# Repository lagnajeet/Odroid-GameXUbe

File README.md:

# Ordoid GameXUbe

A gamecude looking console using Odroid XU4 single board computer. 

Below is a demo video of working of the case. It has the retro arena retropie OS installed in the Board. It can be used with other retro OSes like recalbox or batocera.

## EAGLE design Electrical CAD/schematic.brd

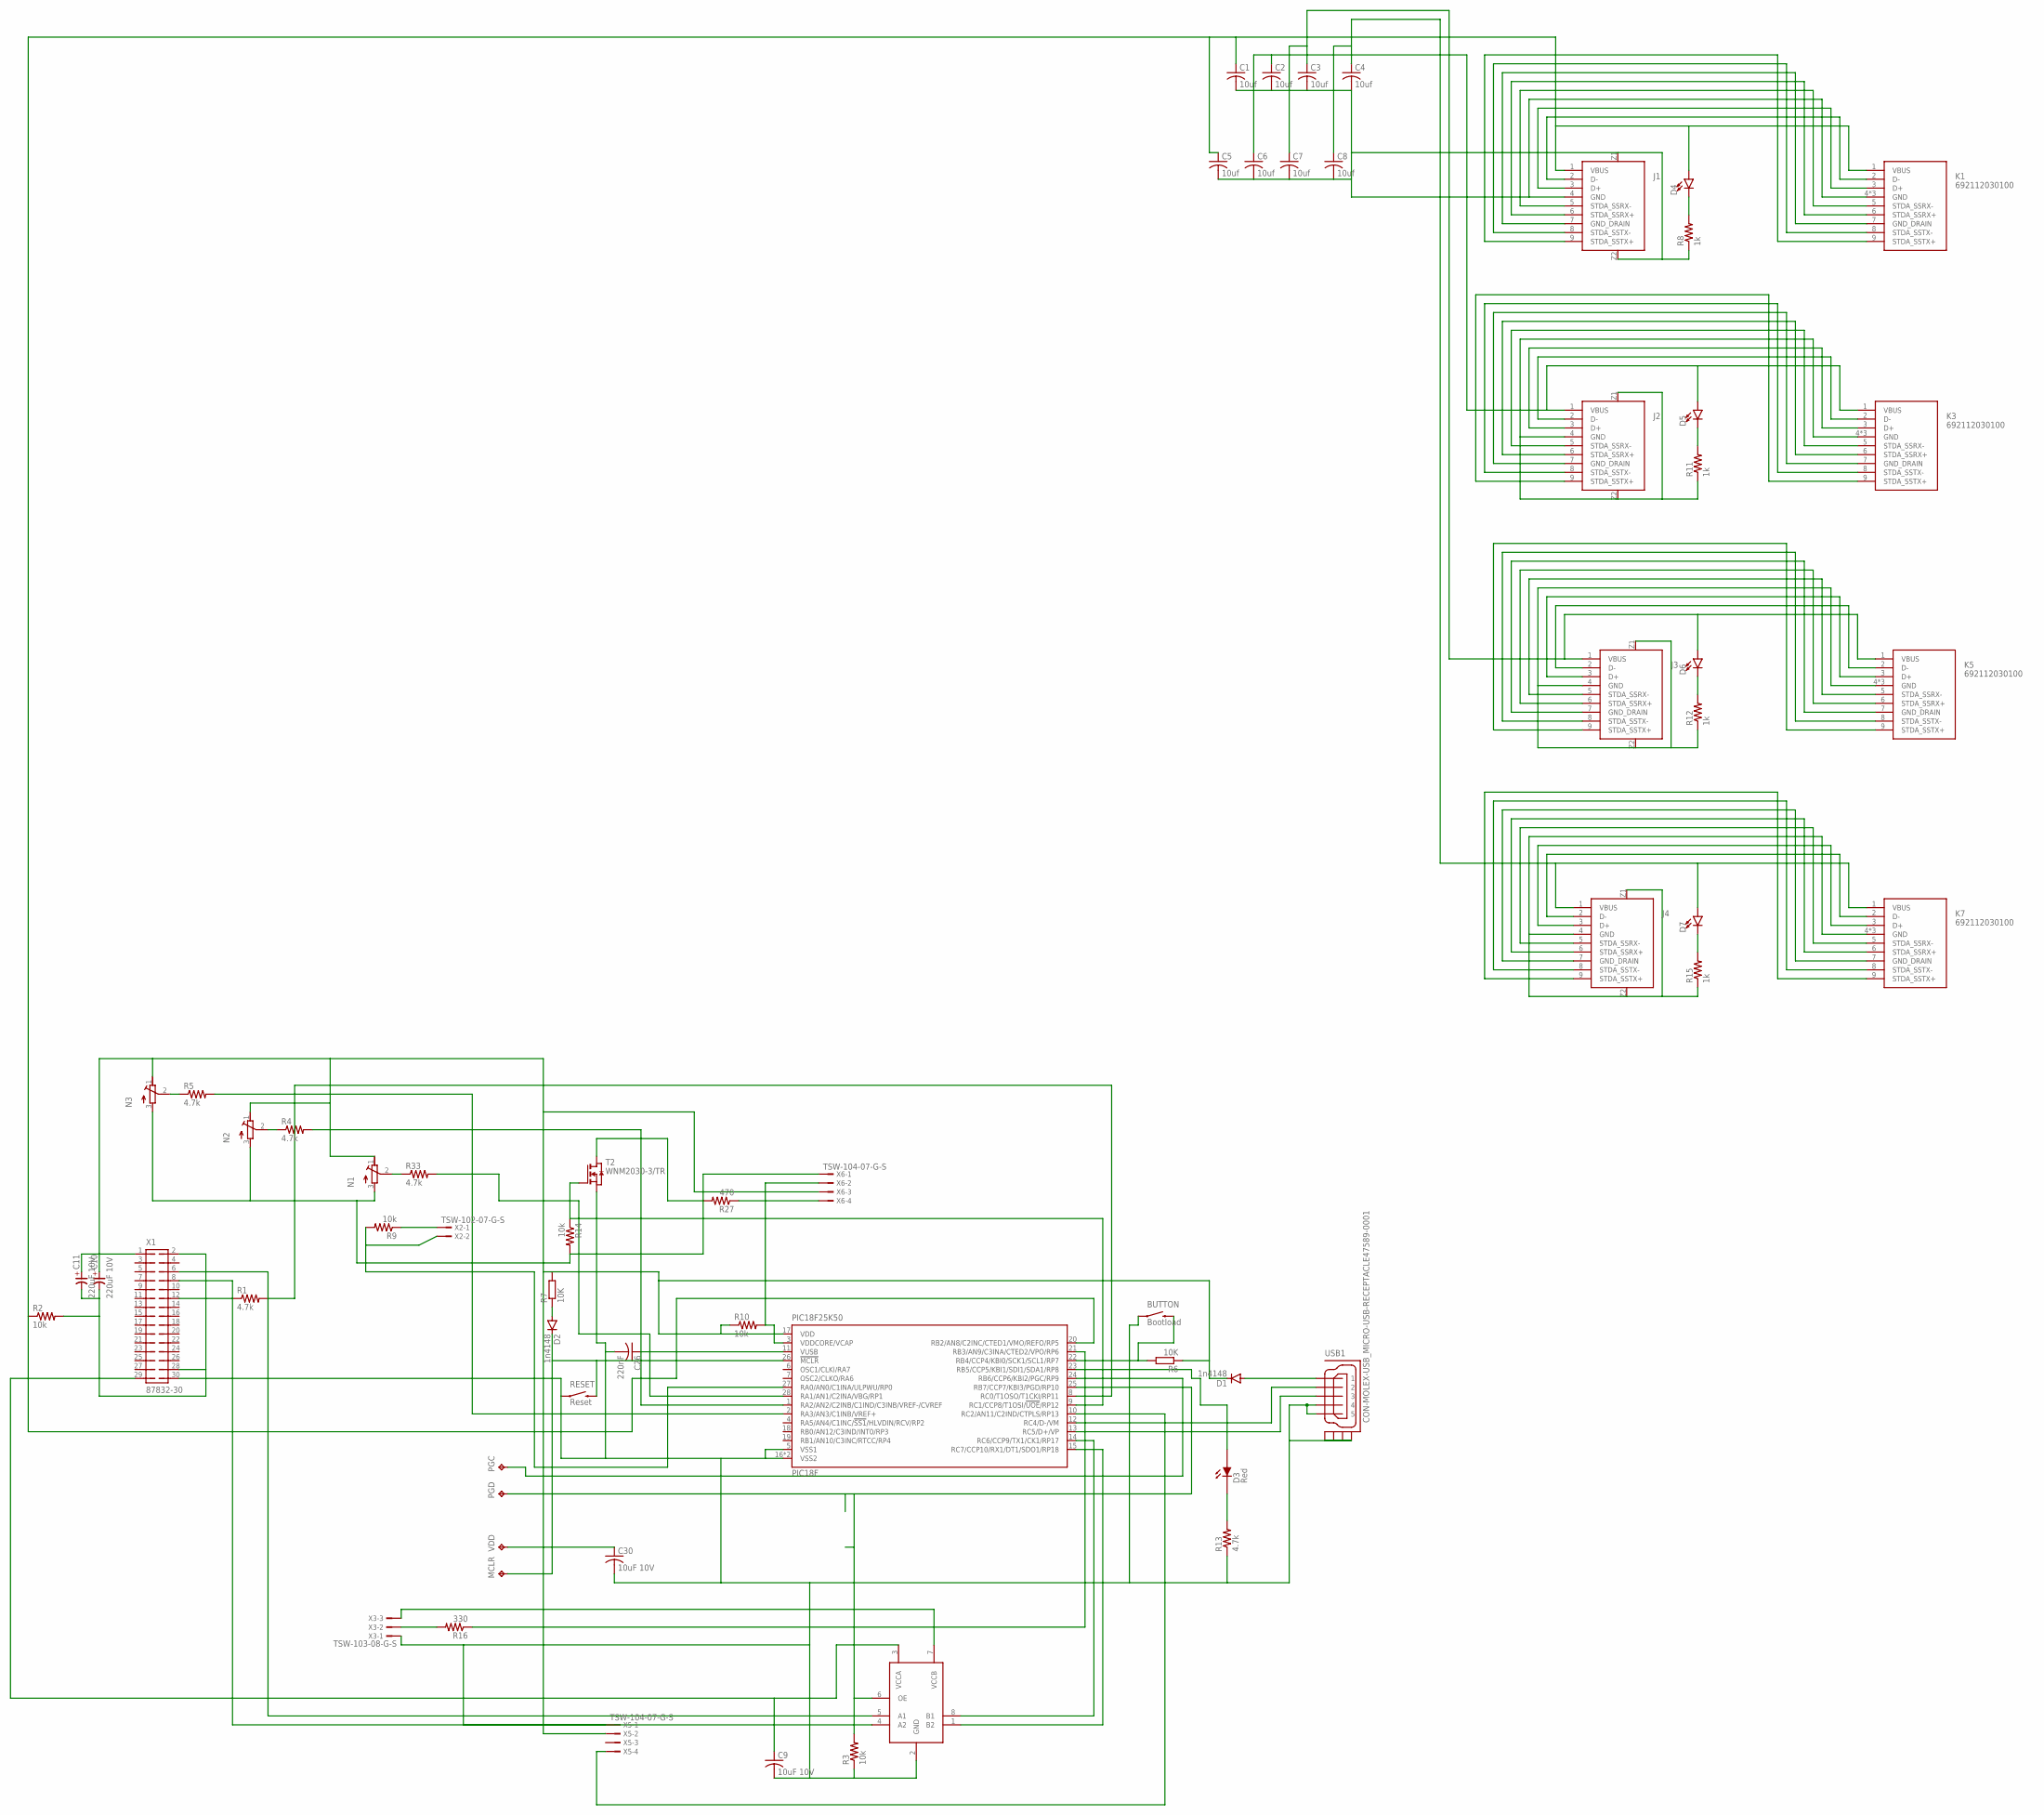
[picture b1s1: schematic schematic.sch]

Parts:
BUTTON: Bootload; BEAGLEBONE_BLUE_SPARKFUN-ELECTROMECHANICAL_TACTILE_SWITCH_S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
C1, C2, C3, C4, C5, C6, C7, C8: 10uf; C0402
C9, C30: 10uF 10V; ADAFRUIT_C0402
C10, C11: 220uF 10V; 3528-TE-B
C26: 220nF; ADAFRUIT_C0402
D1, D2: 1n4148; SPARKFUN-DISCRETESEMI_SOD-123
D3: Red; M-PAD-2.1_0603P
D4, D5, D6, D7: LED-3MM-NO_SILK; LED_3MM-NS
J1, J2, J3, J4: 692121430000
K1, K3, K5, K7: 692112030100
MCLR: TESTPAD_TPTP15SQ; TESTPAD_TP15SQ
N1, N2, N3: R-TRIMM3314J; RTRIM3314J
PGC: TESTPAD_TPTP15SQ; TESTPAD_TP15SQ
PGD: TESTPAD_TPTP15SQ; TESTPAD_TP15SQ
PIC18F25K50: PIC18F; MICROCHIP_QFN28-ML_6X6MM
R1, R4, R5, R13, R33: 4.7k; ADAFRUIT_R0402
R2, R9: 10k; ADAFRUIT_R0402
R3, R10, R14: 10k; R0402
R6, R7: 10K; RCL_R0402
R8, R11, R12, R15: 1k; R0402
R16: 330; R0402
R27: 470; R0402
RESET: Reset; BEAGLEBONE_BLUE_SPARKFUN-ELECTROMECHANICAL_TACTILE_SWITCH_S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
T2: WNM2030-3/TR; SOT723
U1: TXB0102DCUR; VSSOP8
USB1: CON-MOLEX-USB_MICRO-USB-RECEPTACLE47589-0001; CON-MOLEX-USB_47589-0001
VDD: TESTPAD_TPTP15SQ; TESTPAD_TP15SQ
X1: 87832-30
X2: TSW-102-07-G-S; TSW-102-XX-G-S
X3: TSW-103-08-G-S; TSW-103-XX-G-S
X5, X6: TSW-104-07-G-S; TSW-104-XX-G-S

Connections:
GND: BUTTON.1, BUTTON.2 (1), C1.2, C2.2, C3.2, C4.2, C5.2, C6.2, C7.2, C8.2, C9.2, C10.-, C11.-, C26.2, C30.2, J1.4 (GND), J1.Z1, J1.Z2, J2.4 (GND), J2.Z1, J2.Z2, J3.4 (GND), J3.Z1, J3.Z2, J4.4 (GND), J4.Z1, J4.Z2, K1.4 (GND), K1.Z1 (GND), K1.Z2 (GND), K3.4 (GND), K3.Z1 (GND), K3.Z2 (GND), K5.4 (GND), K5.Z1 (GND), K5.Z2 (GND), K7.4 (GND), K7.Z1 (GND), K7.Z2 (GND), N1.3 (A), N2.3 (A), N3.3 (A), PIC18F25K50.5 (VSS1), PIC18F25K50.16 (VSS2), PIC18F25K50.EXP (VSS2), R2.2, R3.1, R8.1, R11.1, R12.1, R13.1, R14.2, R15.1, RESET.1, RESET.2 (1), T2.2 (S), U1.2 (GND), USB1.4, USB1.5, USB1.CASING1 (GND1), USB1.CASING2 (GND2), USB1.CASING3 (GND3), USB1.CASING4 (GND4), X1.2, X1.28, X1.30, X3.1, X5.1, X6.1
unnamed: C1.1, C5.1, D4.A, J1.1 (VBUS), K1.1 (VBUS), PIC18F25K50.20 (RB2/AN8/C2INC/CTED1/VMO/REFO/RP5), R2.1
unnamed: C2.1, C6.1, D5.A, J2.1 (VBUS), K3.1 (VBUS)
unnamed: J1.2 (D-), K1.2 (D-)
unnamed: J1.3 (D+), K1.3 (D+)
unnamed: R1.1, X1.12
unnamed: J2.7 (GND_DRAIN), K3.7 (GND_DRAIN)
unnamed: J1.5 (STDA_SSRX-), K1.5 (STDA_SSRX-)
unnamed: J1.6 (STDA_SSRX+), K1.6 (STDA_SSRX+)
unnamed: C3.1, C7.1, D6.A, J3.1 (VBUS), K5.1 (VBUS)
unnamed: J1.7 (GND_DRAIN), K1.7 (GND_DRAIN)
unnamed: PIC18F25K50.8 (RC0/T1OSO/T1CKI/RP11), R1.2
unnamed: J1.8 (STDA_SSTX-), K1.8 (STDA_SSTX-)
unnamed: J1.9 (STDA_SSTX+), K1.9 (STDA_SSTX+)
unnamed: J3.7 (GND_DRAIN), K5.7 (GND_DRAIN)
unnamed: C4.1, C8.1, D7.A, J4.1 (VBUS), K7.1 (VBUS)
unnamed: C9.1, U1.3 (VCCA), X1.29
unnamed: J4.7 (GND_DRAIN), K7.7 (GND_DRAIN)
unnamed: PIC18F25K50.15 (RC7/CCP10/RX1/DT1/SDO1/RP18), U1.1 (B2)
unnamed: PIC18F25K50.28 (RA1/AN1/C2INA/VBG/RP1), R33.2
unnamed: PIC18F25K50.14 (RC6/CCP9/TX1/CK1/RP17), U1.8 (B1)
unnamed: U1.5 (A1), X1.6
unnamed: U1.4 (A2), X1.8
unnamed: PGC.TP, PIC18F25K50.24 (RB6/CCP6/KBI2/PGC/RP9)
unnamed: PGD.TP, PIC18F25K50.25 (RB7/CCP7/KBI3/PGD/RP10), R3.2, U1.6 (OE)
unnamed: PIC18F25K50.1 (RA2/AN2/C2INB/C1IND/C3INB/VREF-/CVREF), R4.2
unnamed: D4.K (C), R8.2
unnamed: J2.2 (D-), K3.2 (D-)
unnamed: J2.3 (D+), K3.3 (D+)
unnamed: N2.2 (S), R4.1
unnamed: J3.2 (D-), K5.2 (D-)
unnamed: J3.3 (D+), K5.3 (D+)
unnamed: PIC18F25K50.2 (RA3/AN3/C1INB/VREF+), R5.2
unnamed: J4.2 (D-), K7.2 (D-)
unnamed: J4.3 (D+), K7.3 (D+)
unnamed: D5.K (C), R11.2
unnamed: R27.2, T2.3 (D)
unnamed: D3.1 (D_IN), PIC18F25K50.23 (RB5/CCP5/KBI1/SDI1/SDA1/RP8)
unnamed: D3.2 (D_OUT), R13.2
unnamed: N3.2 (S), R5.1
unnamed: D6.K (C), R12.2
unnamed: D7.K (C), R15.2
unnamed: R16.2, X3.2
unnamed: PIC18F25K50.21 (RB3/AN9/C3INA/CTED2/VPO/RP6), R16.1
unnamed: R9.1, X2.1
unnamed: PIC18F25K50.27 (RA0/AN0/C1INA/ULPWU/RP0), R9.2, X2.2
unnamed: PIC18F25K50.9 (RC1/CCP8/T1OSI/!UOE!/RP12), R14.1, T2.1 (G)
unnamed: D1.A, USB1.1
unnamed: C26.1, PIC18F25K50.11 (VUSB)
unnamed: C10.+, C11.+, C30.1, D1.C, N1.1 (E), N2.1 (E), N3.1 (E), PIC18F25K50.17 (VDD), R6.1, R7.2, R10.1, U1.7 (VCCB), VDD.TP, X1.1, X3.3, X5.2, X6.3
unnamed: BUTTON.3 (2), BUTTON.4 (2), PIC18F25K50.22 (RB4/CCP4/KBI0/SCK1/SCL1/RP7), R6.2
unnamed: D2.A, R7.1
unnamed: D2.C, MCLR.TP, PIC18F25K50.26 (!MCLR), RESET.3 (2), RESET.4 (2)
unnamed: PIC18F25K50.10 (RC2/AN11/C2IND/CTPLS/RP13), X5.4
unnamed: R27.1, X6.4
unnamed: N1.2 (S), R33.1
unnamed: J2.5 (STDA_SSRX-), K3.5 (STDA_SSRX-)
unnamed: J2.6 (STDA_SSRX+), K3.6 (STDA_SSRX+)
unnamed: PIC18F25K50.3 (VDDCORE/VCAP), R10.2, X6.2
unnamed: J3.5 (STDA_SSRX-), K5.5 (STDA_SSRX-)
unnamed: J3.6 (STDA_SSRX+), K5.6 (STDA_SSRX+)
unnamed: J4.5 (STDA_SSRX-), K7.5 (STDA_SSRX-)
unnamed: J4.6 (STDA_SSRX+), K7.6 (STDA_SSRX+)
unnamed: J2.8 (STDA_SSTX-), K3.8 (STDA_SSTX-)
unnamed: J2.9 (STDA_SSTX+), K3.9 (STDA_SSTX+)
unnamed: J3.8 (STDA_SSTX-), K5.8 (STDA_SSTX-)
unnamed: J3.9 (STDA_SSTX+), K5.9 (STDA_SSTX+)
unnamed: J4.8 (STDA_SSTX-), K7.8 (STDA_SSTX-)
unnamed: J4.9 (STDA_SSTX+), K7.9 (STDA_SSTX+)
unnamed: PIC18F25K50.12 (RC4/D-/VM), USB1.2
unnamed: PIC18F25K50.13 (RC5/D+/VP), USB1.3

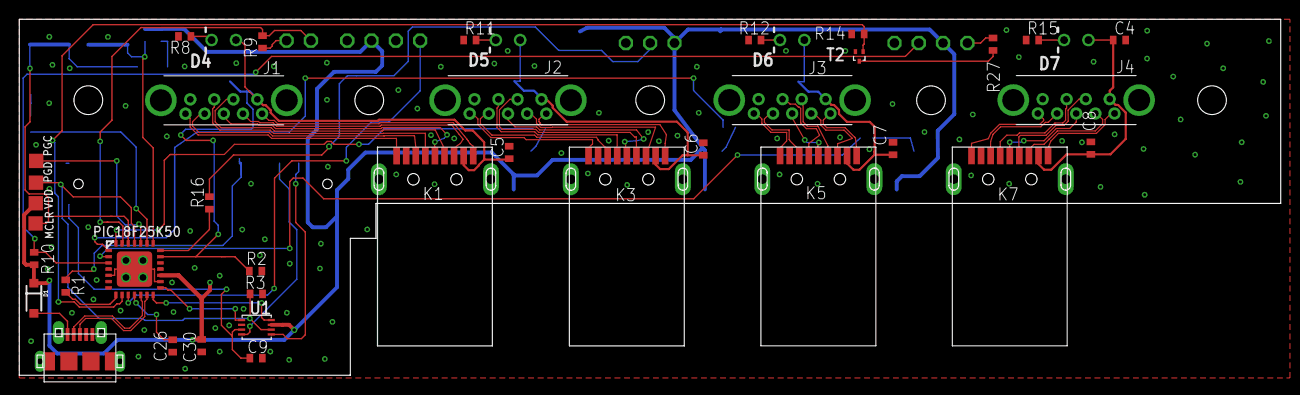
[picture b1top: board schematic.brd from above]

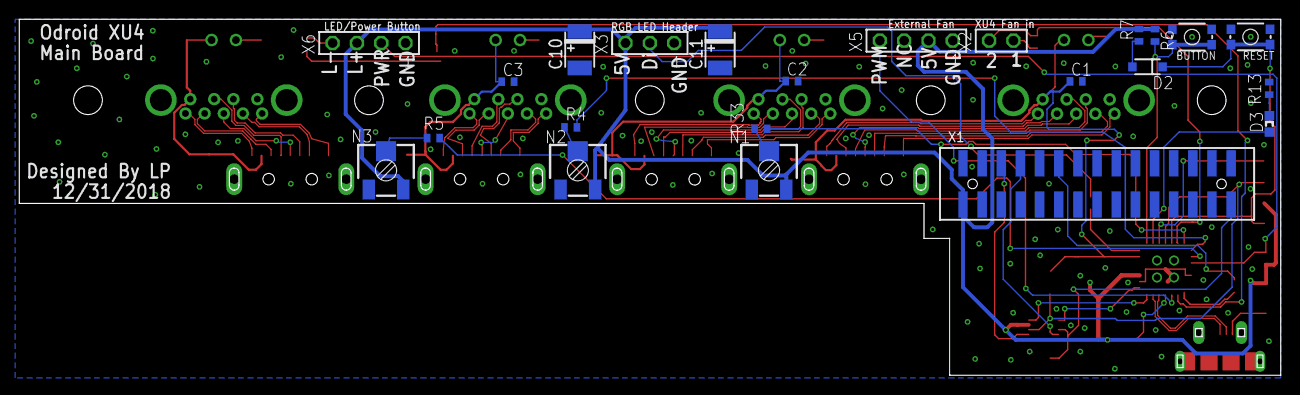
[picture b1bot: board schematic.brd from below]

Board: 2 copper layers, 131.7 x 37.2 mm, 64 parts (23 on the bottom side), 71 nets.

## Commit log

2019-01-01 Initial release
    Initial release of the gamecube look alike gameing console using Odroid XU4 single board computer.

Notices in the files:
parts and their libraries:
Wuerth_Elektronik_eiCan_Communication_Co: Copyright: Würth Elektronik
schematic: (C) 2014 Tomasz Boleslaw CEDRO, cederom@tlen.pl, http://www.tomek.cedro.info.
SparkFun-LED: Licensing: Creative Commons ShareAlike 4.0 International - https://creativecommons.org/licenses/by-sa/4.0
